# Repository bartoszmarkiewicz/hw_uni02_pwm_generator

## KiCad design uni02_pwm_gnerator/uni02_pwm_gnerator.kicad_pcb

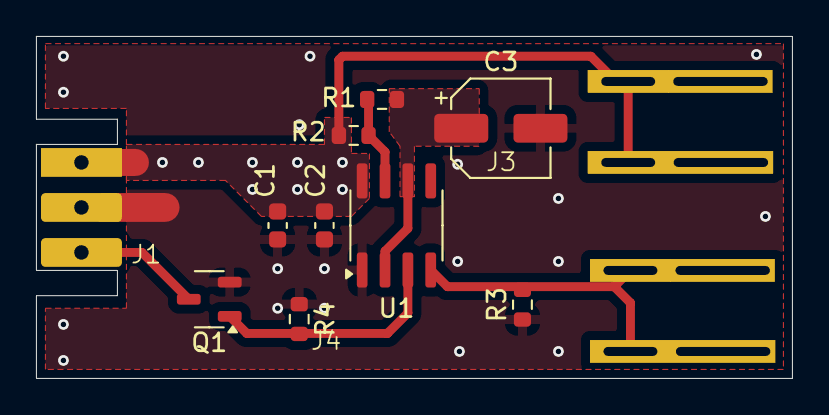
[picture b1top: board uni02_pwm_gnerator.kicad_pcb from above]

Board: 2 copper layers, 42.0 x 19.0 mm, 12 parts (0 on the bottom side), 7 nets.

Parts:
C1, C2: 10n; C_0603_1608Metric
C3: 1uF; CP_Elec_5x5.9
J1: Przewód turbinki ze sterownika; PCB_edge 3 pin
J3, J4: Conn_01x01; Connector_6.3mm
Q1: IRLML28003TRPBF; SOT-23-3
R1, R2: 10k; R_0603_1608Metric
R3, R4: 50k; R_0603_1608Metric
U1: NE555D; SOIC-8_3.9x4.9mm_P1.27mm

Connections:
+15V: C1.1, C2.1, J1.1, J3.1, R2.2, U1.8 (VCC)
GND: C1.2, C2.2, C3.2, J1.2, Q1.2 (S), R3.1, R4.1, U1.1 (GND)
unnamed: R1.2, R2.1, U1.7 (DIS)
OUT: Q1.1 (G), R4.2, U1.3 (Q)
OUT_turbine: J1.3, Q1.3 (D)
TR: C3.1, R1.1, U1.2 (TR), U1.6 (THR)
reset: J4.1, R3.2, U1.4 (R)

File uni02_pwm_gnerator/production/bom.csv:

Designator,Footprint,Quantity,Value,LCSC Part #
"C1, C2",0603,2,10n,
C3,CP_Elec_5x5.9,1,1uF,
J1,PCB_edge 3 pin,1,Przewód turbinki ze sterownika,
"J3, J4",Connector_6.3mm,2,Conn_01x01,
"R1, R2",0603,2,10k,
U1,SOIC-8_3.9x4.9mm_P1.27mm,1,NE555D,

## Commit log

2025-06-30 Init message
2025-06-30 Add init simulation file
2025-06-30 Working simulation
2025-06-30 Updated schematic
2025-07-01 Updated footprints
2025-07-01 Add pcb file
2025-07-01 Final adjustments
2025-07-08 Add JLC codes and production files
2025-07-17 Updated simalation. Additional driver added
2025-07-17 Updated PCB and sch
